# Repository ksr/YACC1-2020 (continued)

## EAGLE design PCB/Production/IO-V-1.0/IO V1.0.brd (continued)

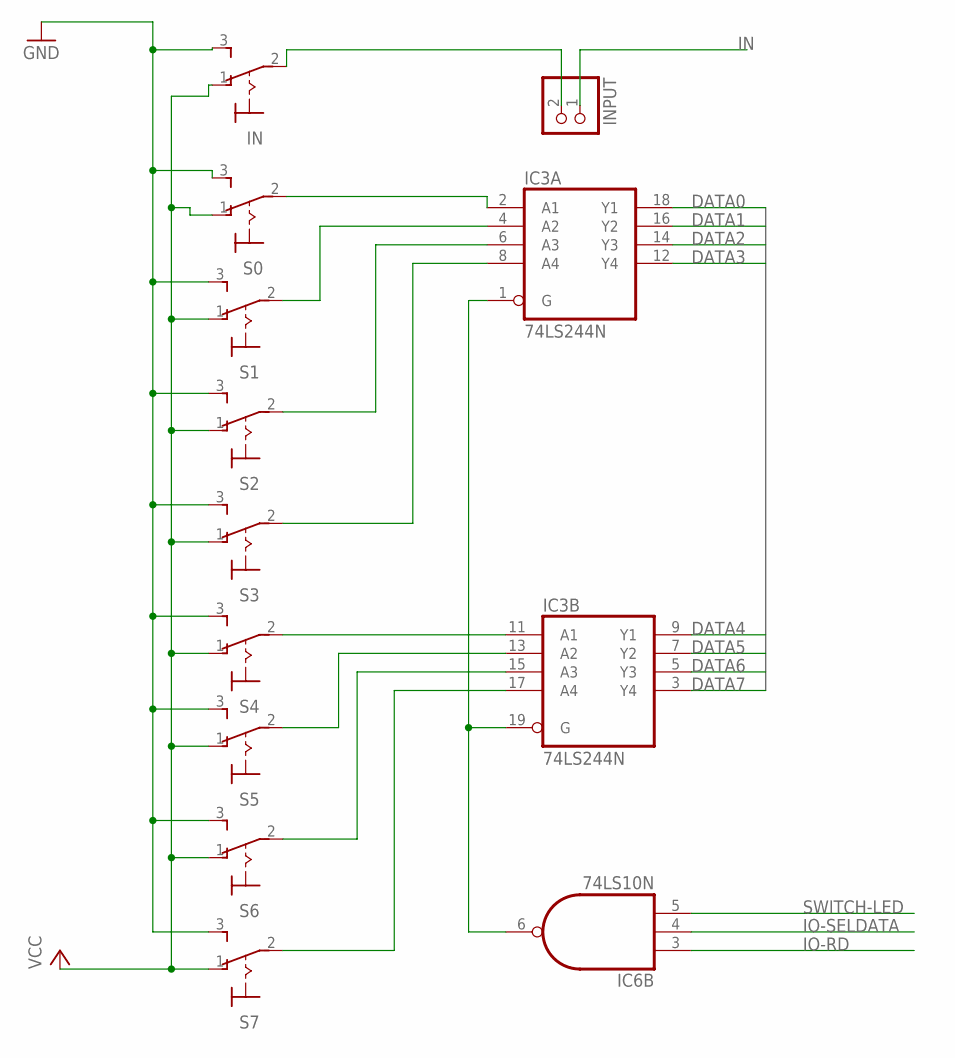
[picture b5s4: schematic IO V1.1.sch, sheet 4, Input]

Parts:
IC3: 74LS244N; DIL20
IC6: 74LS10N; DIL14
IN: M9040P
INPUT: PINHD-1X2; 1X02
S0, S1, S2, S3, S4, S5, S6, S7: M9040P

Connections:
DATA0: IC3.18 (Y1); also elsewhere on the board
DATA1: IC3.16 (Y2); also elsewhere on the board
DATA2: IC3.14 (Y3); also elsewhere on the board
DATA3: IC3.12 (Y4); also elsewhere on the board
DATA4: IC3.9 (Y1); also elsewhere on the board
DATA5: IC3.7 (Y2); also elsewhere on the board
DATA6: IC3.5 (Y3); also elsewhere on the board
DATA7: IC3.3 (Y4); also elsewhere on the board
IN: INPUT.1; also elsewhere on the board
IO-RD: IC6.3 (I0); also elsewhere on the board
IO-SELDATA: IC6.4 (I1); also elsewhere on the board
unnamed: IC3.2 (A1), S0.2
unnamed: IC3.4 (A2), S1.2
unnamed: IC3.6 (A3), S2.2
unnamed: IC3.8 (A4), S3.2
unnamed: IC3.11 (A1), S4.2
unnamed: IC3.13 (A2), S5.2
unnamed: IC3.15 (A3), S6.2
unnamed: IC3.17 (A4), S7.2
unnamed: IC3.1 (G), IC3.19 (G), IC6.6 (O)
unnamed: IN.2, INPUT.2
SWITCH-LED: IC6.5 (I2); also elsewhere on the board
VCC: IC3.20 (VCC), IC6.14 (VCC), IN.1 (O), S0.1 (O), S1.1 (O), S2.1 (O), S3.1 (O), S4.1 (O), S5.1 (O), S6.1 (O), S7.1 (O); also elsewhere on the board

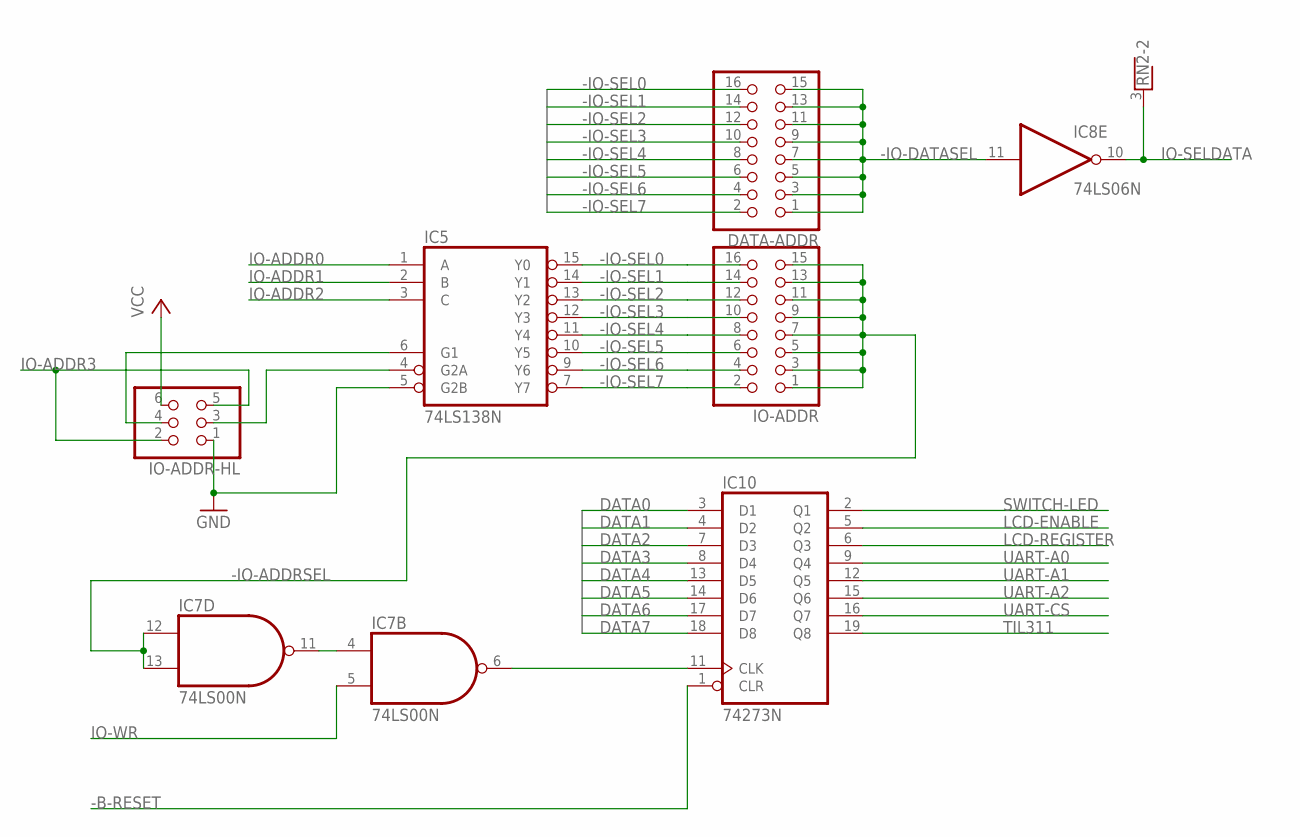
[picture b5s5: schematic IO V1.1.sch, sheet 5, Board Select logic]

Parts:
DATA-ADDR: PINHD-2X8; 2X08
IC5: 74LS138N; DIL16
IC7: 74LS00N; DIL14
IC8: 74LS06N; DIL14
IC10: 74273N; DIL20
IO-ADDR: PINHD-2X8; 2X08
IO-ADDR-HL: PINHD-2X3; 2X03
RN2: RNX6; RN-7

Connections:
-B-RESET: IC10.1 (CLR); also elsewhere on the board
-IO-ADDRSEL: IC7.12 (I0), IC7.13 (I1), IO-ADDR.1, IO-ADDR.3, IO-ADDR.5, IO-ADDR.7, IO-ADDR.9, IO-ADDR.11, IO-ADDR.13, IO-ADDR.15
-IO-DATASEL: DATA-ADDR.1, DATA-ADDR.3, DATA-ADDR.5, DATA-ADDR.7, DATA-ADDR.9, DATA-ADDR.11, DATA-ADDR.13, DATA-ADDR.15, IC8.11 (I)
-IO-SEL0: DATA-ADDR.16, IC5.15 (Y0), IO-ADDR.16
-IO-SEL1: DATA-ADDR.14, IC5.14 (Y1), IO-ADDR.14
-IO-SEL2: DATA-ADDR.12, IC5.13 (Y2), IO-ADDR.12
-IO-SEL3: DATA-ADDR.10, IC5.12 (Y3), IO-ADDR.10
-IO-SEL4: DATA-ADDR.8, IC5.11 (Y4), IO-ADDR.8
-IO-SEL5: DATA-ADDR.6, IC5.10 (Y5), IO-ADDR.6
-IO-SEL6: DATA-ADDR.4, IC5.9 (Y6), IO-ADDR.4
-IO-SEL7: DATA-ADDR.2, IC5.7 (Y7), IO-ADDR.2
DATA0: IC10.3 (D1); also elsewhere on the board
DATA1: IC10.4 (D2); also elsewhere on the board
DATA2: IC10.7 (D3); also elsewhere on the board
DATA3: IC10.8 (D4); also elsewhere on the board
DATA4: IC10.13 (D5); also elsewhere on the board
DATA5: IC10.14 (D6); also elsewhere on the board
DATA6: IC10.17 (D7); also elsewhere on the board
DATA7: IC10.18 (D8); also elsewhere on the board
IO-ADDR0: IC5.1 (A); also elsewhere on the board
IO-ADDR1: IC5.2 (B); also elsewhere on the board
IO-ADDR2: IC5.3 (C); also elsewhere on the board
IO-ADDR3: IO-ADDR-HL.2, IO-ADDR-HL.5; also elsewhere on the board
IO-SELDATA: IC8.10 (O), RN2.3; also elsewhere on the board
IO-WR: IC7.5 (I1); also elsewhere on the board
LCD-ENABLE: IC10.5 (Q2); also elsewhere on the board
LCD-REGISTER: IC10.6 (Q3); also elsewhere on the board
unnamed: IC5.4 (G2A), IO-ADDR-HL.3
unnamed: IC5.6 (G1), IO-ADDR-HL.4
unnamed: IC7.6 (O), IC10.11 (CLK)
unnamed: IC7.4 (I0), IC7.11 (O)
SWITCH-LED: IC10.2 (Q1); also elsewhere on the board
UART-A0: IC10.9 (Q4); also elsewhere on the board
UART-A1: IC10.12 (Q5); also elsewhere on the board
UART-A2: IC10.15 (Q6); also elsewhere on the board
UART-CS: IC10.16 (Q7); also elsewhere on the board
VCC: IC5.16 (VCC), IC7.14 (VCC), IC8.14 (VCC), IC10.20 (VCC), IO-ADDR-HL.6; also elsewhere on the board

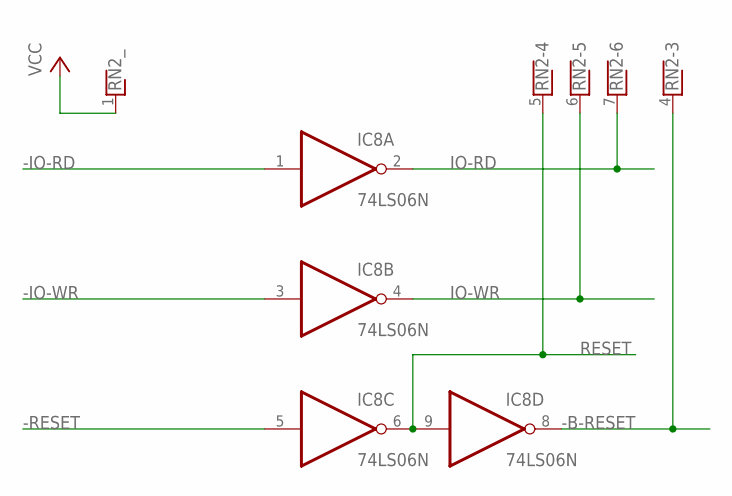
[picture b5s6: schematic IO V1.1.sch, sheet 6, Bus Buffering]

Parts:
IC8: 74LS06N; DIL14
RN2: RNX6; RN-7

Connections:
-B-RESET: IC8.8 (O), RN2.4; also elsewhere on the board
-IO-RD: IC8.1 (I); also elsewhere on the board
-IO-WR: IC8.3 (I); also elsewhere on the board
-RESET: IC8.5 (I); also elsewhere on the board
IO-RD: IC8.2 (O), RN2.7; also elsewhere on the board
IO-WR: IC8.4 (O), RN2.6; also elsewhere on the board
RESET: IC8.6 (O), IC8.9 (I), RN2.5; also elsewhere on the board
VCC: IC8.14 (VCC), RN2.1; also elsewhere on the board

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
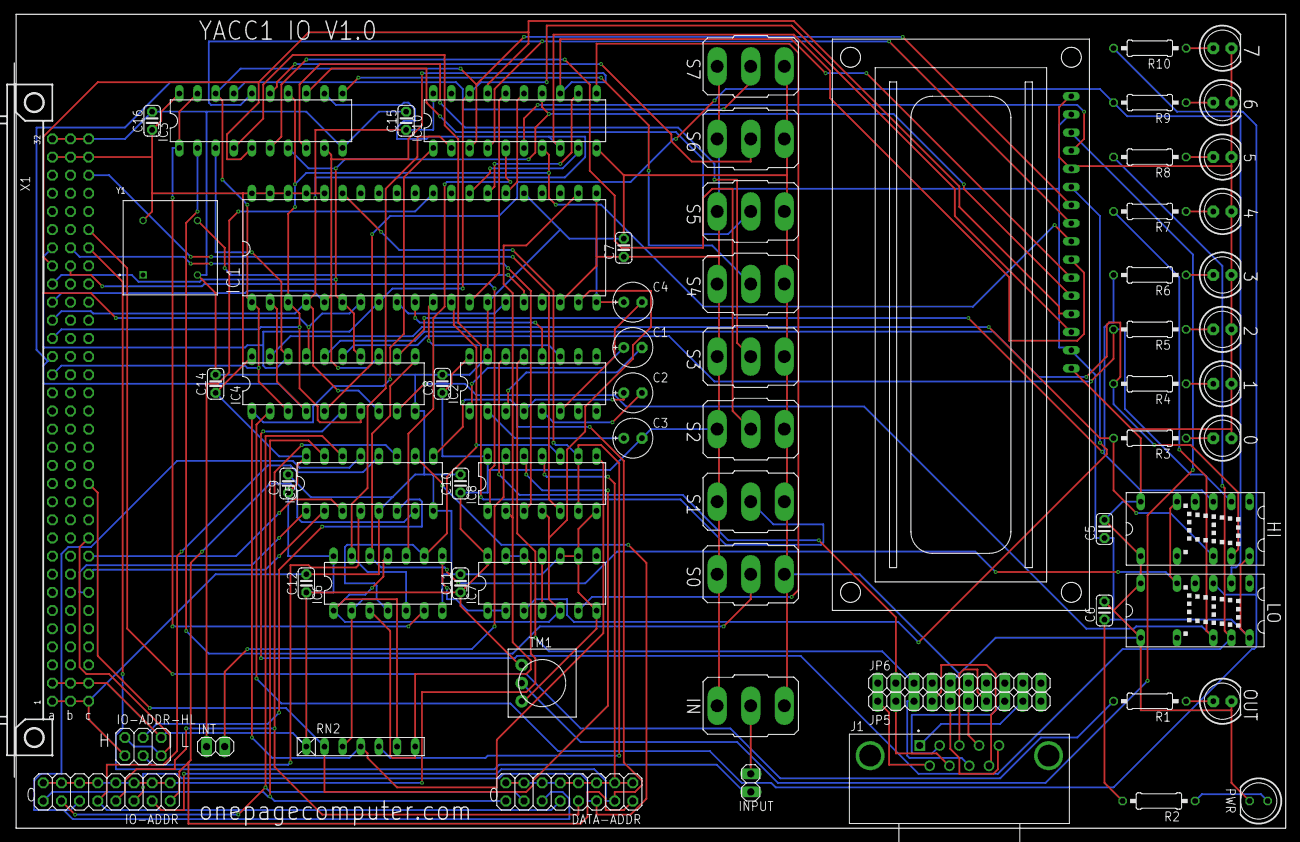
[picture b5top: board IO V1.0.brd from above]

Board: 2 copper layers, 177.8 x 114.0 mm, 68 parts (0 on the bottom side), 101 nets.

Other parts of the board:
JP5, JP6: 1X10

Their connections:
unnamed 117: JP5.1; also elsewhere on the board
unnamed 118: JP5.2; also elsewhere on the board
unnamed 120: JP5.3; also elsewhere on the board
unnamed 121: JP5.4; also elsewhere on the board
unnamed 123: JP5.6; also elsewhere on the board
unnamed 125: JP5.7; also elsewhere on the board
unnamed 127: JP5.8; also elsewhere on the board
unnamed 128: JP5.9; also elsewhere on the board
unnamed 129: JP6.2; also elsewhere on the board
unnamed 130: JP6.3; also elsewhere on the board
